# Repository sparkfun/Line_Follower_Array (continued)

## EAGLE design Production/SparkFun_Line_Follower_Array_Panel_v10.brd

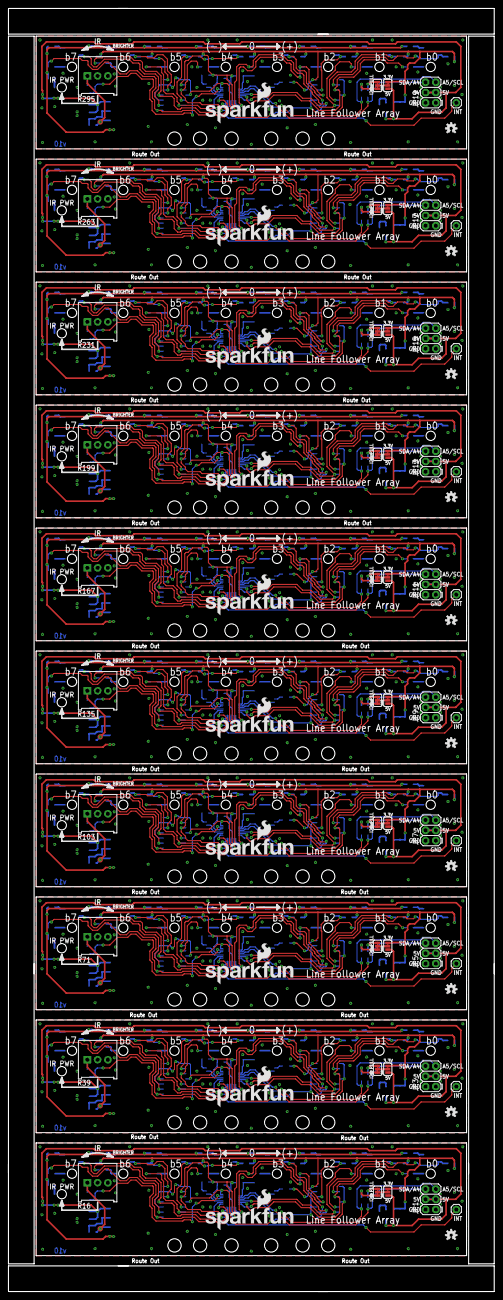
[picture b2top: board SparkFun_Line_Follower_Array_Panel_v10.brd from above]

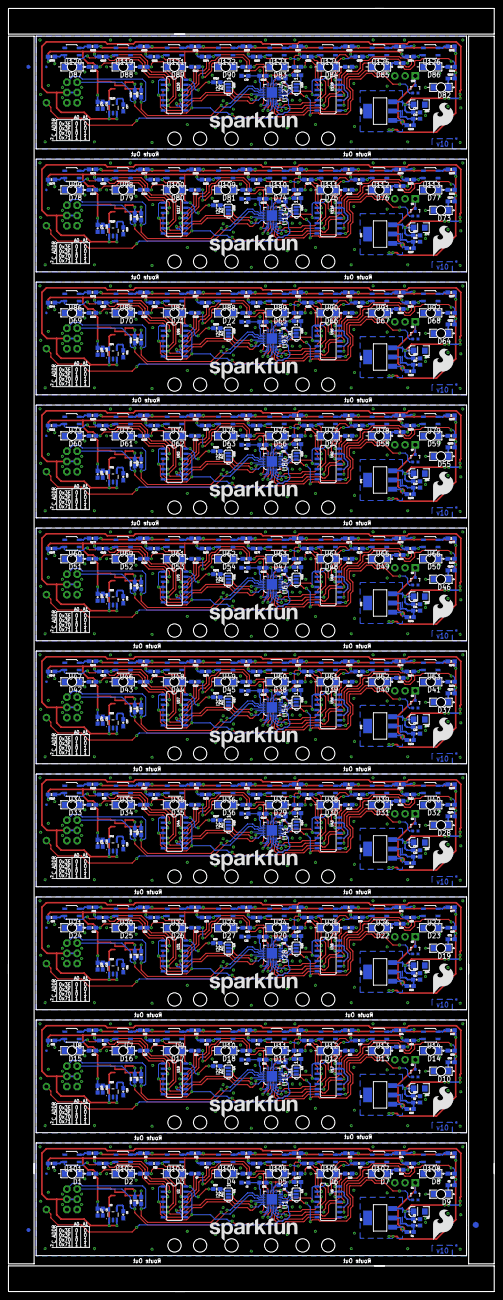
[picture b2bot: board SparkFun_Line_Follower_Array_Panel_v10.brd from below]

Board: 2 copper layers, 120.4 x 318.0 mm, 813 parts (683 on the bottom side), 520 nets.

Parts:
C1, C2, C3, C9, C10, C11, C17, C18, C19, C25, C26, C27, C33, C34, C35, C41, C42, C43, C49, C50, C51, C57, C58, C59, C65, C66, C67, C73, C74, C75: 1.0uF; 0603-CAP
C4, C7, C12, C15, C20, C23, C28, C31, C36, C39, C44, C47, C52, C55, C60, C63, C68, C71, C76, C79: 2.2uF; 0603-CAP
C5, C6, C13, C14, C21, C22, C29, C30, C37, C38, C45, C46, C53, C54, C61, C62, C69, C70, C77, C78: 470pF; 0603-CAP
C8, C16, C24, C32, C40, C48, C56, C64, C72, C80: 10uF; EIA3216
D1, D2, D3, D4, D5, D6, D7, D8, D9, D10, D11, D12, D13, D14, D15, D16, D17, D18, D19, D20, D21, D22, D23, D24, D25, D26, D27, D28, D29, D30, D31, D32, D33, D34, D35, D36, D37, D38, D39, D40, D41, D42, D43, D44, D45, D46, D47, D48, D49, D50, D51, D52, D53, D54, D55, D56, D57, D58, D59, D60, D61, D62, D63, D64, D65, D66, D67, D68, D69, D70, D71, D72, D73, D74, D75, D76, D77, D78, D79, D80, D81, D82, D83, D84, D85, D86, D87, D88, D89, D90: Green; LED-1206-BOTTOM
E$1: FIDUCIAL-1.5X3
E$5, E$6: FIDUCIAL-1X2
FID1, FID2, FID3, FID4, FID5, FID6, FID7, FID8, FID9, FID10, FID11, FID12, FID13, FID14, FID15, FID16, FID17, FID18, FID19, FID20: FIDUCIALUFIDUCIAL; MICRO-FIDUCIAL
JP1, JP3, JP5, JP7, JP9, JP11, JP13, JP15, JP17, JP19: FEMALE 2x3; 2X3
JP2, JP4, JP6, JP8, JP10, JP12, JP14, JP16, JP18, JP20: INT; 1X01
LOGO1, LOGO8, LOGO12, LOGO16, LOGO20, LOGO24, LOGO28, LOGO32, LOGO36, LOGO40: SFE_LOGO_NAME_FLAME.2_INCH; SFE_LOGO_NAME_FLAME_.2
LOGO2, LOGO3, LOGO9, LOGO13, LOGO17, LOGO21, LOGO25, LOGO29, LOGO33, LOGO37: SFE_LOGO_NAME.2_INCH; SFE_LOGO_NAME_.2
LOGO4, LOGO5, LOGO10, LOGO14, LOGO18, LOGO22, LOGO26, LOGO30, LOGO34, LOGO38: SFE_LOGO_FLAME.3_INCH; SFE_LOGO_FLAME_.3
LOGO6, LOGO7, LOGO11, LOGO15, LOGO19, LOGO23, LOGO27, LOGO31, LOGO35, LOGO39: OSHW-LOGOS; OSHW-LOGO-S
Q1, Q2, Q3, Q4, Q5, Q6, Q7, Q8, Q9, Q10: MOSFET-NCHANNEL2N7002PW; SOT323
R1, R15, R30, R32, R33, R34, R50, R51, R63, R64, R65, R82, R83, R95, R96, R97, R114, R115, R127, R128, R129, R146, R147, R159, R160, R161, R178, R179, R191, R192, R193, R210, R211, R223, R224, R225, R242, R243, R255, R256, R257, R274, R275, R287, R288, R289, R306, R307, R319, R320: 4.7K; 0603-RES
R2, R40, R72, R104, R136, R168, R200, R232, R264, R296: 330; 0603-RES
R3, R9, R11, R13, R21, R23, R24, R25, R31, R35, R37, R41, R43, R44, R45, R49, R53, R54, R67, R69, R73, R75, R76, R77, R81, R85, R86, R99, R101, R105, R107, R108, R109, R113, R117, R118, R131, R133, R137, R139, R140, R141, R145, R149, R150, R163, R165, R169, R171, R172, R173, R177, R181, R182, R195, R197, R201, R203, R204, R205, R209, R213, R214, R227, R229, R233, R235, R236, R237, R241, R245, R246, R259, R261, R265, R267, R268, R269, R273, R277, R278, R291, R293, R297, R299, R300, R301, R305, R309, R310: 100; 0603-RES
R4, R10, R12, R14, R22, R26, R27, R28, R29, R36, R38, R42, R46, R47, R48, R52, R66, R68, R70, R74, R78, R79, R80, R84, R98, R100, R102, R106, R110, R111, R112, R116, R130, R132, R134, R138, R142, R143, R144, R148, R162, R164, R166, R170, R174, R175, R176, R180, R194, R196, R198, R202, R206, R207, R208, R212, R226, R228, R230, R234, R238, R239, R240, R244, R258, R260, R262, R266, R270, R271, R272, R276, R290, R292, R294, R298, R302, R303, R304, R308: 68.1k; 0603-RES
R5, R6, R7, R8, R17, R18, R19, R20, R55, R56, R57, R58, R59, R60, R61, R62, R87, R88, R89, R90, R91, R92, R93, R94, R119, R120, R121, R122, R123, R124, R125, R126, R151, R152, R153, R154, R155, R156, R157, R158, R183, R184, R185, R186, R187, R188, R189, R190, R215, R216, R217, R218, R219, R220, R221, R222, R247, R248, R249, R250, R251, R252, R253, R254, R279, R280, R281, R282, R283, R284, R285, R286, R311, R312, R313, R314, R315, R316, R317, R318: 1K; 0603-RES
R16, R39, R71, R103, R135, R167, R199, R231, R263, R295: TSR-3386; 3386U
SJ1, SJ4, SJ9, SJ13, SJ17, SJ21, SJ25, SJ29, SJ33, SJ37: A0; PAD-JUMPER-3-2OF3_NC_BY_PASTE_YES_SILK_FULL_BOX
SJ2, SJ6, SJ10, SJ14, SJ18, SJ22, SJ26, SJ30, SJ34, SJ38: A1; PAD-JUMPER-3-2OF3_NC_BY_PASTE_YES_SILK_FULL_BOX
SJ3, SJ7, SJ11, SJ15, SJ19, SJ23, SJ27, SJ31, SJ35, SJ39: A1; PAD-JUMPER-3-3OF3_NC_BY_TRACE_YES_SILK_FULL_BOX
SJ5, SJ8, SJ12, SJ16, SJ20, SJ24, SJ28, SJ32, SJ36, SJ40: JUMPER-PAD-3-2OF3_NC_BY_TRACE_SMALL; PAD-JUMPER-3-2OF3_NC_BY_TRACE_YES_SILK_FULL_BOX
STANDOFF1, STANDOFF2, STANDOFF3, STANDOFF4, STANDOFF5, STANDOFF6, STANDOFF7, STANDOFF8, STANDOFF9, STANDOFF10, STANDOFF11, STANDOFF12, STANDOFF13, STANDOFF14, STANDOFF15, STANDOFF16, STANDOFF17, STANDOFF18, STANDOFF19, STANDOFF20, STANDOFF21, STANDOFF22, STANDOFF23, STANDOFF24, STANDOFF25, STANDOFF26, STANDOFF27, STANDOFF28, STANDOFF29, STANDOFF30, STANDOFF31, STANDOFF32, STANDOFF33, STANDOFF34, STANDOFF35, STANDOFF36, STANDOFF37, STANDOFF38, STANDOFF39, STANDOFF40, STANDOFF41, STANDOFF42, STANDOFF43, STANDOFF44, STANDOFF45, STANDOFF46, STANDOFF47, STANDOFF48, STANDOFF49, STANDOFF50, STANDOFF51, STANDOFF52, STANDOFF53, STANDOFF54, STANDOFF55, STANDOFF56, STANDOFF57, STANDOFF58, STANDOFF59, STANDOFF60: STAND-OFF
U1, U15, U28, U41, U54, U67, U80, U93, U114, U127: SX1509; QFN-28
U2, U6, U17, U18, U30, U31, U43, U44, U56, U57, U69, U70, U82, U83, U95, U96, U116, U117, U129, U130: 74AC125; SO14
U3, U16, U29, U42, U55, U68, U81, U94, U115, U128: 3.3V/150mA; SOT23-5
U4, U5, U19, U32, U45, U58, U71, U84, U97, U118: LM1117; SOT223
U7, U8, U9, U10, U11, U12, U13, U14, U20, U21, U22, U23, U24, U25, U26, U27, U33, U34, U35, U36, U37, U38, U39, U40, U46, U47, U48, U49, U50, U51, U52, U53, U59, U60, U61, U62, U63, U64, U65, U66, U72, U73, U74, U75, U76, U77, U78, U79, U85, U86, U87, U88, U89, U90, U91, U92, U98, U99, U100, U101, U102, U103, U104, U105, U106, U107, U108, U109, U110, U111, U112, U113, U119, U120, U121, U122, U123, U124, U125, U126: QRE1113

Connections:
!FBLEDEN: U1.14, U2.1, U2.4, U2.10, U2.13, U6.1, U6.4, U6.10, U6.13
!FBLEDEN1: U15.14, U17.1, U17.4, U17.10, U17.13, U18.1, U18.4, U18.10, U18.13
!FBLEDEN2: U28.14, U30.1, U30.4, U30.10, U30.13, U31.1, U31.4, U31.10, U31.13
!FBLEDEN3: U41.14, U43.1, U43.4, U43.10, U43.13, U44.1, U44.4, U44.10, U44.13
!FBLEDEN4: U54.14, U56.1, U56.4, U56.10, U56.13, U57.1, U57.4, U57.10, U57.13
!FBLEDEN5: U67.14, U69.1, U69.4, U69.10, U69.13, U70.1, U70.4, U70.10, U70.13
!FBLEDEN6: U80.14, U82.1, U82.4, U82.10, U82.13, U83.1, U83.4, U83.10, U83.13
!FBLEDEN7: U93.14, U95.1, U95.4, U95.10, U95.13, U96.1, U96.4, U96.10, U96.13
!FBLEDEN8: U114.14, U116.1, U116.4, U116.10, U116.13, U117.1, U117.4, U117.10, U117.13
!FBLEDEN9: U127.14, U129.1, U129.4, U129.10, U129.13, U130.1, U130.4, U130.10, U130.13
!IRLEDEN: Q1.1, U1.13
!IRLEDEN1: Q2.1, U15.13
!IRLEDEN2: Q3.1, U28.13
!IRLEDEN3: Q4.1, U41.13
!IRLEDEN4: Q5.1, U54.13
!IRLEDEN5: Q6.1, U67.13
!IRLEDEN6: Q7.1, U80.13
!IRLEDEN7: Q8.1, U93.13
!IRLEDEN8: Q9.1, U114.13
!IRLEDEN9: Q10.1, U127.13
A0: SJ1.2, U1.26
A1: SJ2.2, U1.10
A2: SJ4.2, U15.26
A3: SJ6.2, U15.10
A4: SJ9.2, U28.26
A5: SJ10.2, U28.10
A6: SJ13.2, U41.26
A7: SJ14.2, U41.10
A8: SJ17.2, U54.26
A9: SJ18.2, U54.10
A10: SJ21.2, U67.26
A11: SJ22.2, U67.10
A12: SJ25.2, U80.26
A13: SJ26.2, U80.10
A14: SJ29.2, U93.26
A15: SJ30.2, U93.10
A16: SJ33.2, U114.26
A17: SJ34.2, U114.10
A18: SJ37.2, U127.26
A19: SJ38.2, U127.10
GND: C1.2, C2.2, C3.2, C4.2, C5.2, C6.2, C7.2, C8.C, D1.C, D2.C, D3.C, D4.C, D5.C, D6.C, D7.C, D8.C, D9.C, JP1.1, JP1.2, Q1.2, R16.2, R16.3, SJ1.3, SJ2.3, U1.3, U1.17, U1.29, U2.7, U3.2, U6.7, U101.2, U101.4, U102.2, U102.4, U103.2, U103.4, U104.2, U104.4, U105.2, U105.4, U106.2, U106.4, U107.2, U107.4, U108.2, U108.4
GND2: C9.2, C10.2, C11.2, C12.2, C13.2, C14.2, C15.2, C16.C, D10.C, D11.C, D12.C, D13.C, D14.C, D15.C, D16.C, D17.C, D18.C, JP3.1, JP3.2, Q2.2, R39.2, R39.3, SJ4.3, SJ6.3, U7.2, U7.4, U8.2, U8.4, U9.2, U9.4, U10.2, U10.4, U11.2, U11.4, U12.2, U12.4, U13.2, U13.4, U14.2, U14.4, U15.3, U15.17, U15.29, U16.2, U17.7, U18.7
GND3: C17.2, C18.2, C19.2, C20.2, C21.2, C22.2, C23.2, C24.C, D19.C, D20.C, D21.C, D22.C, D23.C, D24.C, D25.C, D26.C, D27.C, JP5.1, JP5.2, Q3.2, R71.2, R71.3, SJ9.3, SJ10.3, U20.2, U20.4, U21.2, U21.4, U22.2, U22.4, U23.2, U23.4, U24.2, U24.4, U25.2, U25.4, U26.2, U26.4, U27.2, U27.4, U28.3, U28.17, U28.29, U29.2, U30.7, U31.7
GND4: C25.2, C26.2, C27.2, C28.2, C29.2, C30.2, C31.2, C32.C, D28.C, D29.C, D30.C, D31.C, D32.C, D33.C, D34.C, D35.C, D36.C, JP7.1, JP7.2, Q4.2, R103.2, R103.3, SJ13.3, SJ14.3, U33.2, U33.4, U34.2, U34.4, U35.2, U35.4, U36.2, U36.4, U37.2, U37.4, U38.2, U38.4, U39.2, U39.4, U40.2, U40.4, U41.3, U41.17, U41.29, U42.2, U43.7, U44.7
GND5: C33.2, C34.2, C35.2, C36.2, C37.2, C38.2, C39.2, C40.C, D37.C, D38.C, D39.C, D40.C, D41.C, D42.C, D43.C, D44.C, D45.C, JP9.1, JP9.2, Q5.2, R135.2, R135.3, SJ17.3, SJ18.3, U46.2, U46.4, U47.2, U47.4, U48.2, U48.4, U49.2, U49.4, U50.2, U50.4, U51.2, U51.4, U52.2, U52.4, U53.2, U53.4, U54.3, U54.17, U54.29, U55.2, U56.7, U57.7
GND6: C41.2, C42.2, C43.2, C44.2, C45.2, C46.2, C47.2, C48.C, D46.C, D47.C, D48.C, D49.C, D50.C, D51.C, D52.C, D53.C, D54.C, JP11.1, JP11.2, Q6.2, R167.2, R167.3, SJ21.3, SJ22.3, U59.2, U59.4, U60.2, U60.4, U61.2, U61.4, U62.2, U62.4, U63.2, U63.4, U64.2, U64.4, U65.2, U65.4, U66.2, U66.4, U67.3, U67.17, U67.29, U68.2, U69.7, U70.7
GND7: C49.2, C50.2, C51.2, C52.2, C53.2, C54.2, C55.2, C56.C, D55.C, D56.C, D57.C, D58.C, D59.C, D60.C, D61.C, D62.C, D63.C, JP13.1, JP13.2, Q7.2, R199.2, R199.3, SJ25.3, SJ26.3, U72.2, U72.4, U73.2, U73.4, U74.2, U74.4, U75.2, U75.4, U76.2, U76.4, U77.2, U77.4, U78.2, U78.4, U79.2, U79.4, U80.3, U80.17, U80.29, U81.2, U82.7, U83.7
GND8: C57.2, C58.2, C59.2, C60.2, C61.2, C62.2, C63.2, C64.C, D64.C, D65.C, D66.C, D67.C, D68.C, D69.C, D70.C, D71.C, D72.C, JP15.1, JP15.2, Q8.2, R231.2, R231.3, SJ29.3, SJ30.3, U85.2, U85.4, U86.2, U86.4, U87.2, U87.4, U88.2, U88.4, U89.2, U89.4, U90.2, U90.4, U91.2, U91.4, U92.2, U92.4, U93.3, U93.17, U93.29, U94.2, U95.7, U96.7
GND9: C65.2, C66.2, C67.2, C68.2, C69.2, C70.2, C71.2, C72.C, D73.C, D74.C, D75.C, D76.C, D77.C, D78.C, D79.C, D80.C, D81.C, JP17.1, JP17.2, Q9.2, R263.2, R263.3, SJ33.3, SJ34.3, U98.2, U98.4, U99.2, U99.4, U100.2, U100.4, U109.2, U109.4, U110.2, U110.4, U111.2, U111.4, U112.2, U112.4, U113.2, U113.4, U114.3, U114.17, U114.29, U115.2, U116.7, U117.7
GND10: C73.2, C74.2, C75.2, C76.2, C77.2, C78.2, C79.2, C80.C, D82.C, D83.C, D84.C, D85.C, D86.C, D87.C, D88.C, D89.C, D90.C, JP19.1, JP19.2, Q10.2, R295.2, R295.3, SJ37.3, SJ38.3, U119.2, U119.4, U120.2, U120.4, U121.2, U121.4, U122.2, U122.4, U123.2, U123.4, U124.2, U124.4, U125.2, U125.4, U126.2, U126.4, U127.3, U127.17, U127.29, U128.2, U129.7, U130.7
I2C_PWR: C3.1, C4.1, C7.1, R4.2, R10.2, R12.2, R14.2, R22.2, R26.2, R27.2, R28.2, R31.1, R33.1, R34.1, SJ5.3, U1.4, U1.12, U1.18, U2.14, U3.5, U6.14
I2C_PWR1: C11.1, C12.1, C15.1, R29.2, R36.2, R38.2, R42.2, R46.2, R47.2, R48.2, R52.2, R54.1, R63.1, R64.1, SJ8.3, U15.4, U15.12, U15.18, U16.5, U17.14, U18.14
I2C_PWR2: C19.1, C20.1, C23.1, R66.2, R68.2, R70.2, R74.2, R78.2, R79.2, R80.2, R84.2, R86.1, R95.1, R96.1, SJ12.3, U28.4, U28.12, U28.18, U29.5, U30.14, U31.14
I2C_PWR3: C27.1, C28.1, C31.1, R98.2, R100.2, R102.2, R106.2, R110.2, R111.2, R112.2, R116.2, R118.1, R127.1, R128.1, SJ16.3, U41.4, U41.12, U41.18, U42.5, U43.14, U44.14
I2C_PWR4: C35.1, C36.1, C39.1, R130.2, R132.2, R134.2, R138.2, R142.2, R143.2, R144.2, R148.2, R150.1, R159.1, R160.1, SJ20.3, U54.4, U54.12, U54.18, U55.5, U56.14, U57.14
I2C_PWR5: C43.1, C44.1, C47.1, R162.2, R164.2, R166.2, R170.2, R174.2, R175.2, R176.2, R180.2, R182.1, R191.1, R192.1, SJ24.3, U67.4, U67.12, U67.18, U68.5, U69.14, U70.14
I2C_PWR6: C51.1, C52.1, C55.1, R194.2, R196.2, R198.2, R202.2, R206.2, R207.2, R208.2, R212.2, R214.1, R223.1, R224.1, SJ28.3, U80.4, U80.12, U80.18, U81.5, U82.14, U83.14
I2C_PWR7: C59.1, C60.1, C63.1, R226.2, R228.2, R230.2, R234.2, R238.2, R239.2, R240.2, R244.2, R246.1, R255.1, R256.1, SJ32.3, U93.4, U93.12, U93.18, U94.5, U95.14, U96.14
I2C_PWR8: C67.1, C68.1, C71.1, R258.2, R260.2, R262.2, R266.2, R270.2, R271.2, R272.2, R276.2, R278.1, R287.1, R288.1, SJ36.3, U114.4, U114.12, U114.18, U115.5, U116.14, U117.14
I2C_PWR9: C75.1, C76.1, C79.1, R290.2, R292.2, R294.2, R298.2, R302.2, R303.2, R304.2, R308.2, R310.1, R319.1, R320.1, SJ40.3, U127.4, U127.12, U127.18, U128.5, U129.14, U130.14
INT: JP2.1, U1.9
INT1: JP4.1, U15.9
INT2: JP6.1, U28.9
INT3: JP8.1, U41.9
INT4: JP10.1, U54.9
INT5: JP12.1, U67.9
INT6: JP14.1, U80.9
INT7: JP16.1, U93.9
INT8: JP18.1, U114.9
INT9: JP20.1, U127.9
LED_BIAS: C1.1, R1.1, R2.2, R3.1, R9.1, R11.1, R13.1, R21.1, R23.1, R24.1, R25.1, U5.2, U5.4
LED_BIAS1: C9.1, R15.1, R35.1, R37.1, R40.2, R41.1, R43.1, R44.1, R45.1, R49.1, R53.1, U4.2, U4.4
LED_BIAS2: C17.1, R65.1, R67.1, R69.1, R72.2, R73.1, R75.1, R76.1, R77.1, R81.1, R85.1, U19.2, U19.4
LED_BIAS3: C25.1, R97.1, R99.1, R101.1, R104.2, R105.1, R107.1, R108.1, R109.1, R113.1, R117.1, U32.2, U32.4
LED_BIAS4: C33.1, R129.1, R131.1, R133.1, R136.2, R137.1, R139.1, R140.1, R141.1, R145.1, R149.1, U45.2, U45.4
LED_BIAS5: C41.1, R161.1, R163.1, R165.1, R168.2, R169.1, R171.1, R172.1, R173.1, R177.1, R181.1, U58.2, U58.4
LED_BIAS6: C49.1, R193.1, R195.1, R197.1, R200.2, R201.1, R203.1, R204.1, R205.1, R209.1, R213.1, U71.2, U71.4
LED_BIAS7: C57.1, R225.1, R227.1, R229.1, R232.2, R233.1, R235.1, R236.1, R237.1, R241.1, R245.1, U84.2, U84.4
LED_BIAS8: C65.1, R257.1, R259.1, R261.1, R264.2, R265.1, R267.1, R268.1, R269.1, R273.1, R277.1, U97.2, U97.4
LED_BIAS9: C73.1, R289.1, R291.1, R293.1, R296.2, R297.1, R299.1, R300.1, R301.1, R305.1, R309.1, U118.2, U118.4
unnamed: Q1.3, R1.2, R16.1, U5.1
unnamed: R3.2, U101.1
unnamed: R21.2, U105.1
unnamed: R30.2, SJ3.1
unnamed: D1.A, R5.2
unnamed: C5.1, U3.4
unnamed: D2.A, R6.2
unnamed: R32.2, SJ3.3
unnamed: D3.A, R7.2
unnamed: R34.2, SJ2.1
unnamed: D4.A, R8.2
unnamed: R9.2, U102.1
unnamed: R23.2, U106.1
unnamed: R11.2, U103.1
unnamed: R24.2, U107.1
unnamed: R13.2, U104.1
unnamed: R25.2, U108.1
unnamed: D9.A, R2.1
unnamed: SJ3.2, SJ5.2
unnamed: D5.A, R17.2
unnamed: R33.2, SJ1.1
unnamed: D6.A, R18.2
unnamed: Q2.3, R15.2, R39.1, U4.1
unnamed: D7.A, R19.2
unnamed: R49.2, U8.1
unnamed: D8.A, R20.2
unnamed: D15.A, R59.2
unnamed: D16.A, R60.2
unnamed: D17.A, R61.2
unnamed: D18.A, R62.2
unnamed: R53.2, U7.1
unnamed: R35.2, U9.1
unnamed: R37.2, U10.1
unnamed: D10.A, R40.1
unnamed: D11.A, R55.2
unnamed: D12.A, R56.2
unnamed: D13.A, R57.2
unnamed: D14.A, R58.2
unnamed: R41.2, U11.1
unnamed: R43.2, U12.1
unnamed: R44.2, U13.1
unnamed: R45.2, U14.1
unnamed: C13.1, U16.4
unnamed: R50.2, SJ7.1
unnamed: R51.2, SJ7.3
unnamed: SJ7.2, SJ8.2
unnamed: R64.2, SJ6.1
unnamed: R63.2, SJ4.1
unnamed: Q3.3, R65.2, R71.1, U19.1
unnamed: R81.2, U21.1
unnamed: D24.A, R91.2
unnamed: D25.A, R92.2
unnamed: D26.A, R93.2
unnamed: D27.A, R94.2
unnamed: R85.2, U20.1
unnamed: R67.2, U22.1
unnamed: R69.2, U23.1
unnamed: D19.A, R72.1
unnamed: D20.A, R87.2
unnamed: D21.A, R88.2
unnamed: D22.A, R89.2
unnamed: D23.A, R90.2
unnamed: R73.2, U24.1
unnamed: R75.2, U25.1
unnamed: R76.2, U26.1
unnamed: R77.2, U27.1
unnamed: C21.1, U29.4
unnamed: R82.2, SJ11.1
unnamed: R83.2, SJ11.3
unnamed: SJ11.2, SJ12.2
unnamed: R96.2, SJ10.1
unnamed: R95.2, SJ9.1
unnamed: Q4.3, R97.2, R103.1, U32.1
unnamed: R113.2, U34.1
unnamed: D33.A, R123.2
unnamed: D34.A, R124.2
unnamed: D35.A, R125.2
unnamed: D36.A, R126.2
unnamed: R117.2, U33.1
unnamed: R99.2, U35.1
unnamed: R101.2, U36.1
unnamed: D28.A, R104.1
unnamed: D29.A, R119.2
unnamed: D30.A, R120.2
unnamed: D31.A, R121.2
unnamed: D32.A, R122.2
unnamed: R105.2, U37.1
unnamed: R107.2, U38.1
unnamed: R108.2, U39.1
unnamed: R109.2, U40.1
unnamed: C29.1, U42.4
unnamed: R114.2, SJ15.1
unnamed: R115.2, SJ15.3
unnamed: SJ15.2, SJ16.2
unnamed: R128.2, SJ14.1
unnamed: R127.2, SJ13.1
unnamed: Q5.3, R129.2, R135.1, U45.1
unnamed: R145.2, U47.1
unnamed: D42.A, R155.2
unnamed: D43.A, R156.2
unnamed: D44.A, R157.2
unnamed: D45.A, R158.2
unnamed: R149.2, U46.1
unnamed: R131.2, U48.1
unnamed: R133.2, U49.1
unnamed: D37.A, R136.1
unnamed: D38.A, R151.2
unnamed: D39.A, R152.2
unnamed: D40.A, R153.2
unnamed: D41.A, R154.2
unnamed: R137.2, U50.1
unnamed: R139.2, U51.1
unnamed: R140.2, U52.1
unnamed: R141.2, U53.1
unnamed: C37.1, U55.4
unnamed: R146.2, SJ19.1
unnamed: R147.2, SJ19.3
unnamed: SJ19.2, SJ20.2
unnamed: R160.2, SJ18.1
unnamed: R159.2, SJ17.1
unnamed: Q6.3, R161.2, R167.1, U58.1
unnamed: R177.2, U60.1
unnamed: D51.A, R187.2
unnamed: D52.A, R188.2
unnamed: D53.A, R189.2
unnamed: D54.A, R190.2
unnamed: R181.2, U59.1
unnamed: R163.2, U61.1
unnamed: R165.2, U62.1
unnamed: D46.A, R168.1
unnamed: D47.A, R183.2
unnamed: D48.A, R184.2
unnamed: D49.A, R185.2
unnamed: D50.A, R186.2
unnamed: R169.2, U63.1
unnamed: R171.2, U64.1
unnamed: R172.2, U65.1
unnamed: R173.2, U66.1
unnamed: C45.1, U68.4
unnamed: R178.2, SJ23.1
unnamed: R179.2, SJ23.3
unnamed: SJ23.2, SJ24.2
unnamed: R192.2, SJ22.1
unnamed: R191.2, SJ21.1
unnamed: Q7.3, R193.2, R199.1, U71.1
unnamed: R209.2, U73.1
unnamed: D60.A, R219.2
unnamed: D61.A, R220.2
unnamed: D62.A, R221.2
unnamed: D63.A, R222.2
unnamed: R213.2, U72.1
unnamed: R195.2, U74.1
unnamed: R197.2, U75.1
unnamed: D55.A, R200.1
unnamed: D56.A, R215.2
unnamed: D57.A, R216.2
unnamed: D58.A, R217.2
unnamed: D59.A, R218.2
unnamed: R201.2, U76.1
unnamed: R203.2, U77.1
unnamed: R204.2, U78.1
unnamed: R205.2, U79.1
unnamed: C53.1, U81.4
unnamed: R210.2, SJ27.1
unnamed: R211.2, SJ27.3
unnamed: SJ27.2, SJ28.2
unnamed: R224.2, SJ26.1
unnamed: R223.2, SJ25.1
unnamed: Q8.3, R225.2, R231.1, U84.1
unnamed: R241.2, U86.1
unnamed: D69.A, R251.2
unnamed: D70.A, R252.2
unnamed: D71.A, R253.2
unnamed: D72.A, R254.2
unnamed: R245.2, U85.1
unnamed: R227.2, U87.1
unnamed: R229.2, U88.1
unnamed: D64.A, R232.1
unnamed: D65.A, R247.2
unnamed: D66.A, R248.2
unnamed: D67.A, R249.2
unnamed: D68.A, R250.2
unnamed: R233.2, U89.1
unnamed: R235.2, U90.1
unnamed: R236.2, U91.1
unnamed: R237.2, U92.1
unnamed: C61.1, U94.4
unnamed: R242.2, SJ31.1
unnamed: R243.2, SJ31.3
unnamed: SJ31.2, SJ32.2
unnamed: R256.2, SJ30.1
unnamed: R255.2, SJ29.1
unnamed: Q9.3, R257.2, R263.1, U97.1
unnamed: R273.2, U99.1
unnamed: D78.A, R283.2
unnamed: D79.A, R284.2
unnamed: D80.A, R285.2
unnamed: D81.A, R286.2
unnamed: R277.2, U98.1
unnamed: R259.2, U100.1
unnamed: R261.2, U109.1
unnamed: D73.A, R264.1
unnamed: D74.A, R279.2
unnamed: D75.A, R280.2
unnamed: D76.A, R281.2
unnamed: D77.A, R282.2
unnamed: R265.2, U110.1
unnamed: R267.2, U111.1
unnamed: R268.2, U112.1
unnamed: R269.2, U113.1
unnamed: C69.1, U115.4
unnamed: R274.2, SJ35.1
unnamed: R275.2, SJ35.3
unnamed: SJ35.2, SJ36.2
unnamed: R288.2, SJ34.1
unnamed: R287.2, SJ33.1
unnamed: Q10.3, R289.2, R295.1, U118.1
unnamed: R305.2, U120.1
unnamed: D87.A, R315.2
unnamed: D88.A, R316.2
unnamed: D89.A, R317.2
unnamed: D90.A, R318.2
unnamed: R309.2, U119.1
unnamed: R291.2, U121.1
unnamed: R293.2, U122.1
unnamed: D82.A, R296.1
unnamed: D83.A, R311.2
unnamed: D84.A, R312.2
unnamed: D85.A, R313.2
unnamed: D86.A, R314.2
unnamed: R297.2, U123.1
unnamed: R299.2, U124.1
unnamed: R300.2, U125.1
unnamed: R301.2, U126.1
unnamed: C77.1, U128.4
unnamed: R306.2, SJ39.1
unnamed: R307.2, SJ39.3
unnamed: SJ39.2, SJ40.2
unnamed: R320.2, SJ38.1
unnamed: R319.2, SJ37.1
SCL: JP1.5, R30.1, U1.25
SCL1: JP3.5, R50.1, U15.25
SCL2: JP5.5, R82.1, U28.25
SCL3: JP7.5, R114.1, U41.25
SCL4: JP9.5, R146.1, U54.25
SCL5: JP11.5, R178.1, U67.25
SCL6: JP13.5, R210.1, U80.25
SCL7: JP15.5, R242.1, U93.25
SCL8: JP17.5, R274.1, U114.25
SCL9: JP19.5, R306.1, U127.25
SDA: JP1.6, R32.1, U1.24
SDA1: JP3.6, R51.1, U15.24
SDA2: JP5.6, R83.1, U28.24
SDA3: JP7.6, R115.1, U41.24
SDA4: JP9.6, R147.1, U54.24
SDA5: JP11.6, R179.1, U67.24
SDA6: JP13.6, R211.1, U80.24
SDA7: JP15.6, R243.1, U93.24
SDA8: JP17.6, R275.1, U114.24
SDA9: JP19.6, R307.1, U127.24
SEN0: R4.1, U2.2, U101.3
SEN0BUF: R5.1, U1.27, U2.3
SEN0BUF1: R59.1, U15.27, U18.3
SEN0BUF2: R91.1, U28.27, U31.3
SEN0BUF3: R123.1, U41.27, U44.3
SEN0BUF4: R155.1, U54.27, U57.3
SEN0BUF5: R187.1, U67.27, U70.3
SEN0BUF6: R219.1, U80.27, U83.3
SEN0BUF7: R251.1, U93.27, U96.3
SEN0BUF8: R283.1, U114.27, U117.3
SEN0BUF9: R315.1, U127.27, U130.3
SEN1: R10.1, U2.5, U102.3
SEN1BUF: R6.1, U1.28, U2.6
SEN1BUF1: R60.1, U15.28, U18.6
SEN1BUF2: R92.1, U28.28, U31.6
SEN1BUF3: R124.1, U41.28, U44.6
SEN1BUF4: R156.1, U54.28, U57.6
SEN1BUF5: R188.1, U67.28, U70.6
SEN1BUF6: R220.1, U80.28, U83.6
SEN1BUF7: R252.1, U93.28, U96.6
SEN1BUF8: R284.1, U114.28, U117.6
SEN1BUF9: R316.1, U127.28, U130.6
SEN2: R12.1, U2.12, U103.3
SEN2BUF: R7.1, U1.1, U2.11
SEN2BUF1: R61.1, U15.1, U18.11
SEN2BUF2: R93.1, U28.1, U31.11
SEN2BUF3: R125.1, U41.1, U44.11
SEN2BUF4: R157.1, U54.1, U57.11
SEN2BUF5: R189.1, U67.1, U70.11
SEN2BUF6: R221.1, U80.1, U83.11
SEN2BUF7: R253.1, U93.1, U96.11
SEN2BUF8: R285.1, U114.1, U117.11
SEN2BUF9: R317.1, U127.1, U130.11
SEN3: R14.1, U2.9, U104.3
SEN3BUF: R8.1, U1.2, U2.8
SEN3BUF1: R62.1, U15.2, U18.8
SEN3BUF2: R94.1, U28.2, U31.8
SEN3BUF3: R126.1, U41.2, U44.8
SEN3BUF4: R158.1, U54.2, U57.8
SEN3BUF5: R190.1, U67.2, U70.8
SEN3BUF6: R222.1, U80.2, U83.8
SEN3BUF7: R254.1, U93.2, U96.8
SEN3BUF8: R286.1, U114.2, U117.8
SEN3BUF9: R318.1, U127.2, U130.8
SEN4: R22.1, U6.2, U105.3
SEN4BUF: R17.1, U1.5, U6.3
SEN4BUF1: R55.1, U15.5, U17.3
SEN4BUF2: R87.1, U28.5, U30.3
SEN4BUF3: R119.1, U41.5, U43.3
SEN4BUF4: R151.1, U54.5, U56.3
SEN4BUF5: R183.1, U67.5, U69.3
SEN4BUF6: R215.1, U80.5, U82.3
SEN4BUF7: R247.1, U93.5, U95.3
SEN4BUF8: R279.1, U114.5, U116.3
SEN4BUF9: R311.1, U127.5, U129.3
SEN5: R26.1, U6.5, U106.3
SEN5BUF: R18.1, U1.6, U6.6
SEN5BUF1: R56.1, U15.6, U17.6
SEN5BUF2: R88.1, U28.6, U30.6
SEN5BUF3: R120.1, U41.6, U43.6
SEN5BUF4: R152.1, U54.6, U56.6
SEN5BUF5: R184.1, U67.6, U69.6
SEN5BUF6: R216.1, U80.6, U82.6
SEN5BUF7: R248.1, U93.6, U95.6
SEN5BUF8: R280.1, U114.6, U116.6
SEN5BUF9: R312.1, U127.6, U129.6
SEN6: R27.1, U6.12, U107.3
SEN6BUF: R19.1, U1.7, U6.11
SEN6BUF1: R57.1, U15.7, U17.11
SEN6BUF2: R89.1, U28.7, U30.11
SEN6BUF3: R121.1, U41.7, U43.11
SEN6BUF4: R153.1, U54.7, U56.11
SEN6BUF5: R185.1, U67.7, U69.11
SEN6BUF6: R217.1, U80.7, U82.11
SEN6BUF7: R249.1, U93.7, U95.11
SEN6BUF8: R281.1, U114.7, U116.11
SEN6BUF9: R313.1, U127.7, U129.11
SEN7: R28.1, U6.9, U108.3
SEN7BUF: R20.1, U1.8, U6.8
SEN7BUF1: R58.1, U15.8, U17.8
SEN7BUF2: R90.1, U28.8, U30.8
SEN7BUF3: R122.1, U41.8, U43.8
SEN7BUF4: R154.1, U54.8, U56.8
SEN7BUF5: R186.1, U67.8, U69.8
SEN7BUF6: R218.1, U80.8, U82.8
SEN7BUF7: R250.1, U93.8, U95.8
SEN7BUF8: R282.1, U114.8, U116.8
SEN7BUF9: R314.1, U127.8, U129.8
SEN8: R52.1, U8.3, U18.2
SEN9: R29.1, U7.3, U18.5
SEN10: R36.1, U9.3, U18.12
SEN11: R38.1, U10.3, U18.9
SEN12: R42.1, U11.3, U17.2
SEN13: R46.1, U12.3, U17.5
SEN14: R47.1, U13.3, U17.12
SEN15: R48.1, U14.3, U17.9
SEN16: R84.1, U21.3, U31.2
SEN17: R66.1, U20.3, U31.5
SEN18: R68.1, U22.3, U31.12
SEN19: R70.1, U23.3, U31.9
SEN20: R74.1, U24.3, U30.2
SEN21: R78.1, U25.3, U30.5
SEN22: R79.1, U26.3, U30.12
SEN23: R80.1, U27.3, U30.9
SEN24: R116.1, U34.3, U44.2
SEN25: R98.1, U33.3, U44.5
SEN26: R100.1, U35.3, U44.12
SEN27: R102.1, U36.3, U44.9
SEN28: R106.1, U37.3, U43.2
SEN29: R110.1, U38.3, U43.5
SEN30: R111.1, U39.3, U43.12
SEN31: R112.1, U40.3, U43.9
SEN32: R148.1, U47.3, U57.2
SEN33: R130.1, U46.3, U57.5
SEN34: R132.1, U48.3, U57.12
SEN35: R134.1, U49.3, U57.9
SEN36: R138.1, U50.3, U56.2
SEN37: R142.1, U51.3, U56.5
SEN38: R143.1, U52.3, U56.12
SEN39: R144.1, U53.3, U56.9
SEN40: R180.1, U60.3, U70.2
SEN41: R162.1, U59.3, U70.5
SEN42: R164.1, U61.3, U70.12
SEN43: R166.1, U62.3, U70.9
SEN44: R170.1, U63.3, U69.2
SEN45: R174.1, U64.3, U69.5
SEN46: R175.1, U65.3, U69.12
SEN47: R176.1, U66.3, U69.9
SEN48: R212.1, U73.3, U83.2
SEN49: R194.1, U72.3, U83.5
SEN50: R196.1, U74.3, U83.12
SEN51: R198.1, U75.3, U83.9
SEN52: R202.1, U76.3, U82.2
SEN53: R206.1, U77.3, U82.5
SEN54: R207.1, U78.3, U82.12
SEN55: R208.1, U79.3, U82.9
SEN56: R244.1, U86.3, U96.2
SEN57: R226.1, U85.3, U96.5
SEN58: R228.1, U87.3, U96.12
SEN59: R230.1, U88.3, U96.9
SEN60: R234.1, U89.3, U95.2
SEN61: R238.1, U90.3, U95.5
SEN62: R239.1, U91.3, U95.12
SEN63: R240.1, U92.3, U95.9
SEN64: R276.1, U99.3, U117.2
SEN65: R258.1, U98.3, U117.5
SEN66: R260.1, U100.3, U117.12
SEN67: R262.1, U109.3, U117.9
SEN68: R266.1, U110.3, U116.2
SEN69: R270.1, U111.3, U116.5
SEN70: R271.1, U112.3, U116.12
SEN71: R272.1, U113.3, U116.9
SEN72: R308.1, U120.3, U130.2
SEN73: R290.1, U119.3, U130.5
SEN74: R292.1, U121.3, U130.12
SEN75: R294.1, U122.3, U130.9
SEN76: R298.1, U123.3, U129.2
SEN77: R302.1, U124.3, U129.5
SEN78: R303.1, U125.3, U129.12
SEN79: R304.1, U126.3, U129.9
VCC: C2.1, C8.A, JP1.3, JP1.4, SJ5.1, U3.1, U3.3, U5.3
VCC1: C10.1, C16.A, JP3.3, JP3.4, SJ8.1, U4.3, U16.1, U16.3
VCC2: C18.1, C24.A, JP5.3, JP5.4, SJ12.1, U19.3, U29.1, U29.3
VCC3: C26.1, C32.A, JP7.3, JP7.4, SJ16.1, U32.3, U42.1, U42.3
VCC4: C34.1, C40.A, JP9.3, JP9.4, SJ20.1, U45.3, U55.1, U55.3
VCC5: C42.1, C48.A, JP11.3, JP11.4, SJ24.1, U58.3, U68.1, U68.3
VCC6: C50.1, C56.A, JP13.3, JP13.4, SJ28.1, U71.3, U81.1, U81.3
VCC7: C58.1, C64.A, JP15.3, JP15.4, SJ32.1, U84.3, U94.1, U94.3
VCC8: C66.1, C72.A, JP17.3, JP17.4, SJ36.1, U97.3, U115.1, U115.3
VCC9: C74.1, C80.A, JP19.3, JP19.4, SJ40.1, U118.3, U128.1, U128.3
~RESET: C6.1, R31.2, U1.23
~RESET1: C14.1, R54.2, U15.23
~RESET2: C22.1, R86.2, U28.23
~RESET3: C30.1, R118.2, U41.23
~RESET4: C38.1, R150.2, U54.23
~RESET5: C46.1, R182.2, U67.23
~RESET6: C54.1, R214.2, U80.23
~RESET7: C62.1, R246.2, U93.23
~RESET8: C70.1, R278.2, U114.23
~RESET9: C78.1, R310.2, U127.23

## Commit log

2015-03-17 Reorganized directory structure
2015-03-17 Initial commit for first example
2015-03-18 Added a sketch that can simply go around a line
2015-03-18 added a couple more sketches. May remove in the future
2015-03-19 added first schematic part
2015-03-31 Layout commit
2015-04-02 Working on docs
2015-04-02 Added readme content
2015-04-07 Shrunk PCB
2015-04-08 logos and 47 measures and t_place added, Oh my!
2015-04-08 about ready for proto submit
2015-04-09 fixed for QC
2015-05-29 fixed half the issues
2015-05-29 Ran DRC, fixing aesthetic
2015-05-29 ready for review of prototype 2 (v03)
2015-06-01 Ready for proto
2015-06-04 Fixed github/qc finds
2015-07-09 v04: IR LED power ctrl, regulated receiver supply
2015-07-09 Fixed QC issues
2015-08-21 V_1.0 update
2015-08-21 Fixed rev number and readme
2015-08-21 fixed tag
2015-08-24 Renamed project
2015-08-27 created panel v10
2015-10-14 finishing documentation for release
2015-10-14 Squashed 'Libraries/Arduino/' content from commit 02afd32
    git-subtree-dir: Libraries/Arduino
    git-subtree-split: 02afd32d755ee1969facbfc80f71514770557b3f
2016-01-11 Squashed 'Libraries/Arduino/' changes from 02afd32..2914662
    git-subtree-dir: Libraries/Arduino
    git-subtree-split: 29146627b9eda56a58f48e0abae9e124bb2415a8
